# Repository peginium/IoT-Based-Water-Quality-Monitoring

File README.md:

# 💧 Smart Water Quality Monitoring System

An end-to-end, IoT-based Smart Water Quality Monitoring Station designed for real-time, in-situ analysis of water health. The system utilizes edge-processing to calculate a universal **Water Quality Index (WQI)** based on multiple sensor readings and streams JSON-formatted data wirelessly to a custom web dashboard.

Developed as a functional hardware-software integration project by **Chipware Labs**.

## ✨ Key Features
* **Real-Time Data Acquisition:** Simultaneously measures Temperature (°C), Total Dissolved Solids (TDS in ppm), and pH levels.
* **Edge Computing:** Performs hardware-level temperature compensation and WQI calculation directly on the MSP430 MCU.
* **Dual Visualization:** * *Local:* 0.96" I2C OLED display for immediate on-site readings.
  * *Remote:* Wireless transmission to a browser-based dashboard.
* **Web Serial API Dashboard:** Zero-server architecture. Connects directly to the HC-05 Bluetooth module via the browser to parse and display real-time JSON data.
* **Cascade Power Management:** Custom power distribution using LM7805 (5V) and LM1117T (3.3V) to ensure thermal stability and sensor accuracy.

## 🛠️ Hardware Architecture

### Components Used
* **MCU:** Texas Instruments MSP430G2553
* **Temperature Sensor:** DS18B20 (Waterproof, 1-Wire)
* **TDS Sensor:** Analog TDS Meter
* **pH Sensor:** DFRobot Gravity Analog pH Meter V2
* **Display:** Waveshare 0.96" OLED (I2C Mode)
* **Wireless Module:** HC-05 Bluetooth (UART)
* **Power:** 9V Battery + LM7805 & LM1117T-3.3 Regulators

### Pinout & Wiring Connections
| Module / Sensor | Pin / Function | MSP430G2553 Pin | Notes |
| :--- | :--- | :--- | :--- |
| **DS18B20** | DQ (Data) | `P2.0` | Requires a 4.7kΩ pull-up resistor to 3.3V. |
| **Analog TDS** | A0 (Signal) | `P1.4` (A4) | ADC input. Needs temperature compensation. |
| **Gravity pH V2** | A (Signal) | `P1.5` (A5) | ADC input. |
| **OLED Display**| SCL (Clock) | `P1.6` | I2C SCL. Requires 4.7kΩ pull-up resistor. |
| **OLED Display**| SDA (Data) | `P1.7` | I2C SDA. Requires 4.7kΩ pull-up resistor. |
| **HC-05** | TXD | `P1.1` (RXD) | Cross-connection for UART. |
| **HC-05** | RXD | `P1.2` (TXD) | Cross-connection for UART. |

> **⚠️ Important Hardware Note:** Ensure that the OLED's `CS` and `DC` pins are grounded to lock it into I2C mode (Address: `0x3C`), and tie the `RES` pin to 3.3V.

## 💻 Software Architecture
The embedded firmware is written in **C** using **Code Composer Studio (CCS)**. It focuses on lightweight operations to fit within the 16KB flash memory limit of the MSP430G2553.

* **Sensor Calibration:** Linear interpolation is used for pH, and active temperature compensation formula is applied to TDS readings.
* **WQI Algorithm:** A weighted arithmetic mean algorithm converts raw parameters into a single score (0-100) and categorizes water into *Excellent, Good, Poor, or Undrinkable*.
* **JSON Formatting:** To prevent memory overflow, custom string parsing algorithms are implemented instead of standard `sprintf` libraries. Data is packaged as `{"t":25.5,"tds":145,"ph":7.1,"wqi":85}\r\n`.

## 🚀 Installation & Setup

### 1. Embedded Firmware
1. Clone this repository: `git clone https://github.com/peginium/IoT-Based-Water-Quality-Monitoring.git`
2. Open **Code Composer Studio (CCS)** and import the project.
3. Build the project and flash it to the MSP430 Launchpad.
4. Wire the components according to the table above.

### 2. Web Dashboard
1. Power up the hardware system.
2. Pair your computer with the **HC-05** Bluetooth module (Default PIN is usually `1234` or `0000`).
3. Open the `index.html` file (located in the `/web` folder of this repo) using Google Chrome or Microsoft Edge.
4. Click the **Connect** button on the web page and select the Bluetooth COM port from the browser prompt.
5. Watch the real-time data flow!

## 👨‍💻 Author & Credits
* **Arhan Özcan**

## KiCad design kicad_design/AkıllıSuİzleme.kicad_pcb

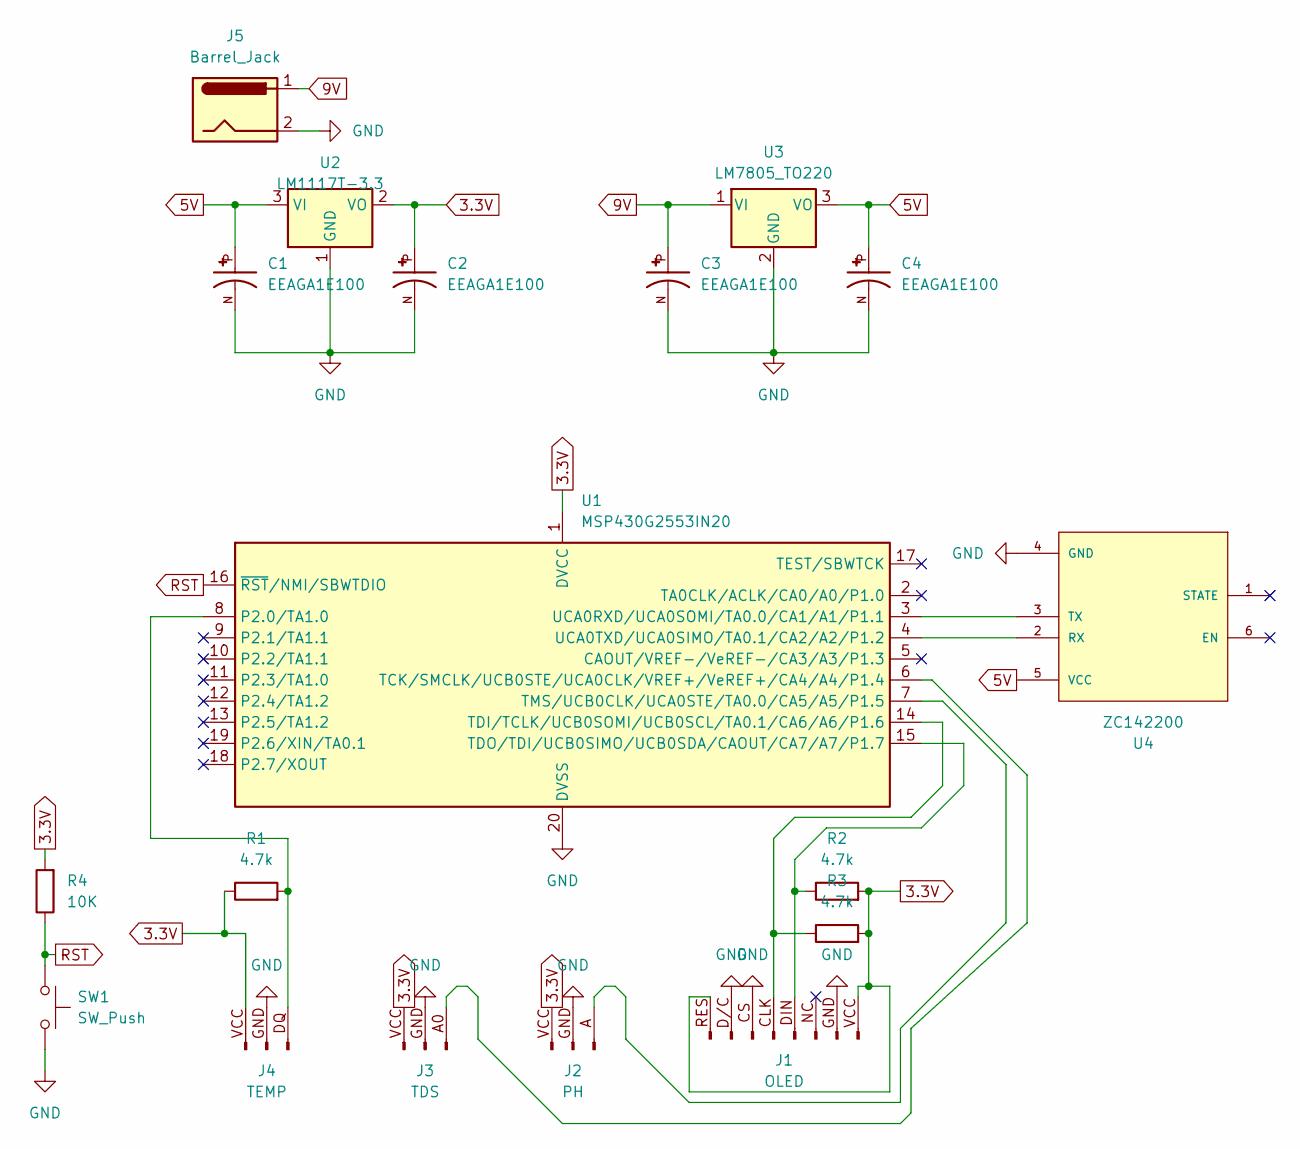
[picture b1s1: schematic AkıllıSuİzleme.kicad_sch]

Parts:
C1, C2, C3, C4: EEAGA1E100; C_Radial_D6.3mm_H7.0mm_P2.50mm; PARTREV 28-FEB-20
J1: OLED; PinHeader_1x08_P2.54mm_Vertical
J2: PH; PinHeader_1x03_P2.54mm_Vertical
J3: TDS; PinHeader_1x03_P2.54mm_Vertical
J4: TEMP; PinHeader_1x03_P2.54mm_Vertical
J5: Barrel_Jack; BarrelJack_SwitchcraftConxall_RAPC10U_Horizontal
R1, R2, R3: 4.7k; R_Axial_DIN0207_L6.3mm_D2.5mm_P10.16mm_Horizontal
R4: 10K; R_Axial_DIN0207_L6.3mm_D2.5mm_P10.16mm_Horizontal
SW1: SW_Push; SW_PUSH_1P1T_6x3.5mm_H5.0_APEM_MJTP1250
U1: MSP430G2553IN20; DIP-20_W7.62mm
U2: LM1117T-3.3; TO-220-3_Vertical
U3: LM7805_TO220; TO-220-3_Vertical
U4: ZC142200; MODULE_ZC142200; PARTREV N/A

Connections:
3.3V: C2.P, J1.RES (Pin_1), J1.VCC (Pin_8), J2.VCC (Pin_1), J3.VCC (Pin_1), J4.VCC (Pin_1), R1.1, R2.2, R3.2, R4.2, U1.1 (DVCC), U2.2 (VO)
5V: C1.P, C4.P, U2.3 (VI), U3.3 (VO), U4.5 (VCC)
9V: C3.P, J5.1, U3.1 (VI)
GND: C1.N, C2.N, C3.N, C4.N, J1.CS (Pin_3), J1.D/C (Pin_2), J1.GND (Pin_7), J2.GND (Pin_2), J3.GND (Pin_2), J4.GND (Pin_2), J5.2, SW1.2, U1.20 (DVSS), U2.1 (GND), U3.2 (GND), U4.4 (GND)
unnamed: J1.CLK (Pin_4), R3.1, U1.14 (TDI/TCLK/UCB0SOMI/UCB0SCL/TA0.1/CA6/A6/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)
unnamed: J1.DIN (Pin_5), R2.1, U1.15 (TDO/TDI/UCB0SIMO/UCB0SDA/CAOUT/CA7/A7/P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)
unnamed: J2.A (Pin_3), U1.7 (TMS/UCB0CLK/UCA0STE/TA0.0/CA5/A5/P1.5)
unnamed: J3.A0 (Pin_3), U1.6 (TCK/SMCLK/UCB0STE/UCA0CLK/VREF+/VeREF+/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)
unnamed: J4.DQ (Pin_3), R1.2, U1.8 (P2.0/TA1.0)
unnamed: U1.3 (UCA0RXD/UCA0SOMI/TA0.0/CA1/A1/P1.1), U4.3 (TX)
unnamed: U1.4 (UCA0TXD/UCA0SIMO/TA0.1/CA2/A2/P1.2), U4.2 (RX)
RST: R4.1, SW1.1, U1.16 (~RST/NMI/SBWTDIO)

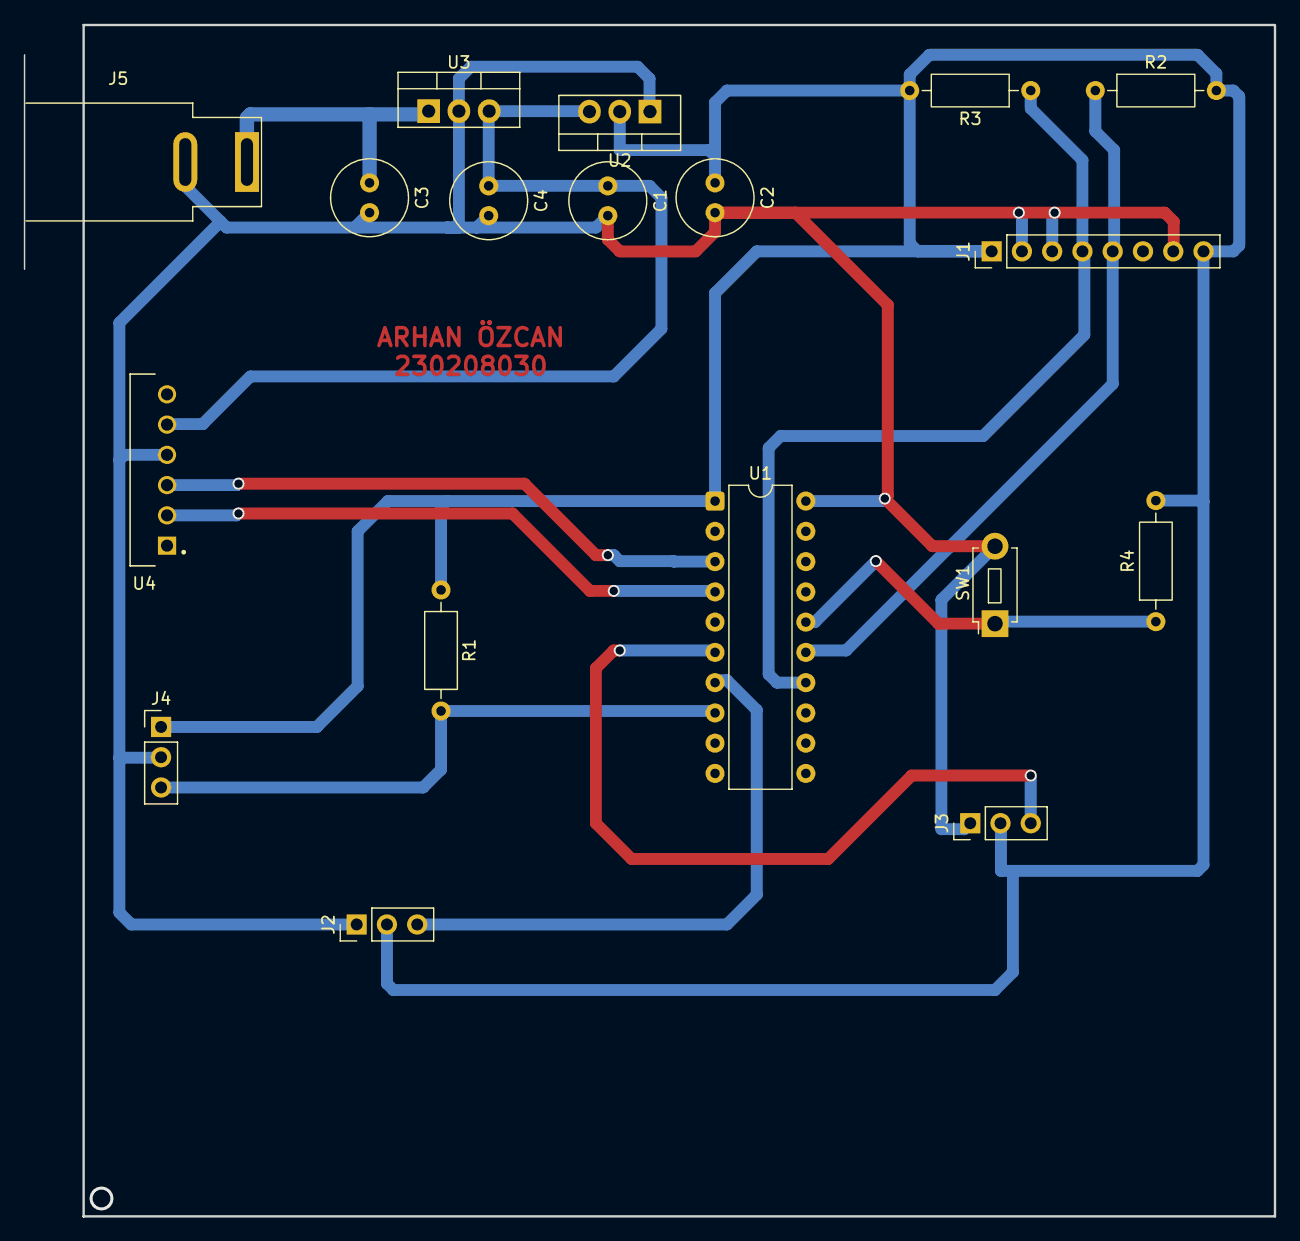
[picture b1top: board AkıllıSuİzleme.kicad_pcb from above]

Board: 2 copper layers, 104.9 x 100.0 mm, 18 parts (0 on the bottom side), 12 nets.
